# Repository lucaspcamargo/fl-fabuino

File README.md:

# FABUINO Project Files + Presentation Materials

The FABUINO is a simple arduino clone that is meant to be assembled by hand, during a workshop. It relies on an FTDI cable for programming.

This repo contains the project files and materials for presentation. The first instance of this workshop was given at FabLab Joinville in March 2020.
It was a good opportunity to project the spirit of DIY-electronics on the participants.

If anyone wants to use this for something just hit me up :)

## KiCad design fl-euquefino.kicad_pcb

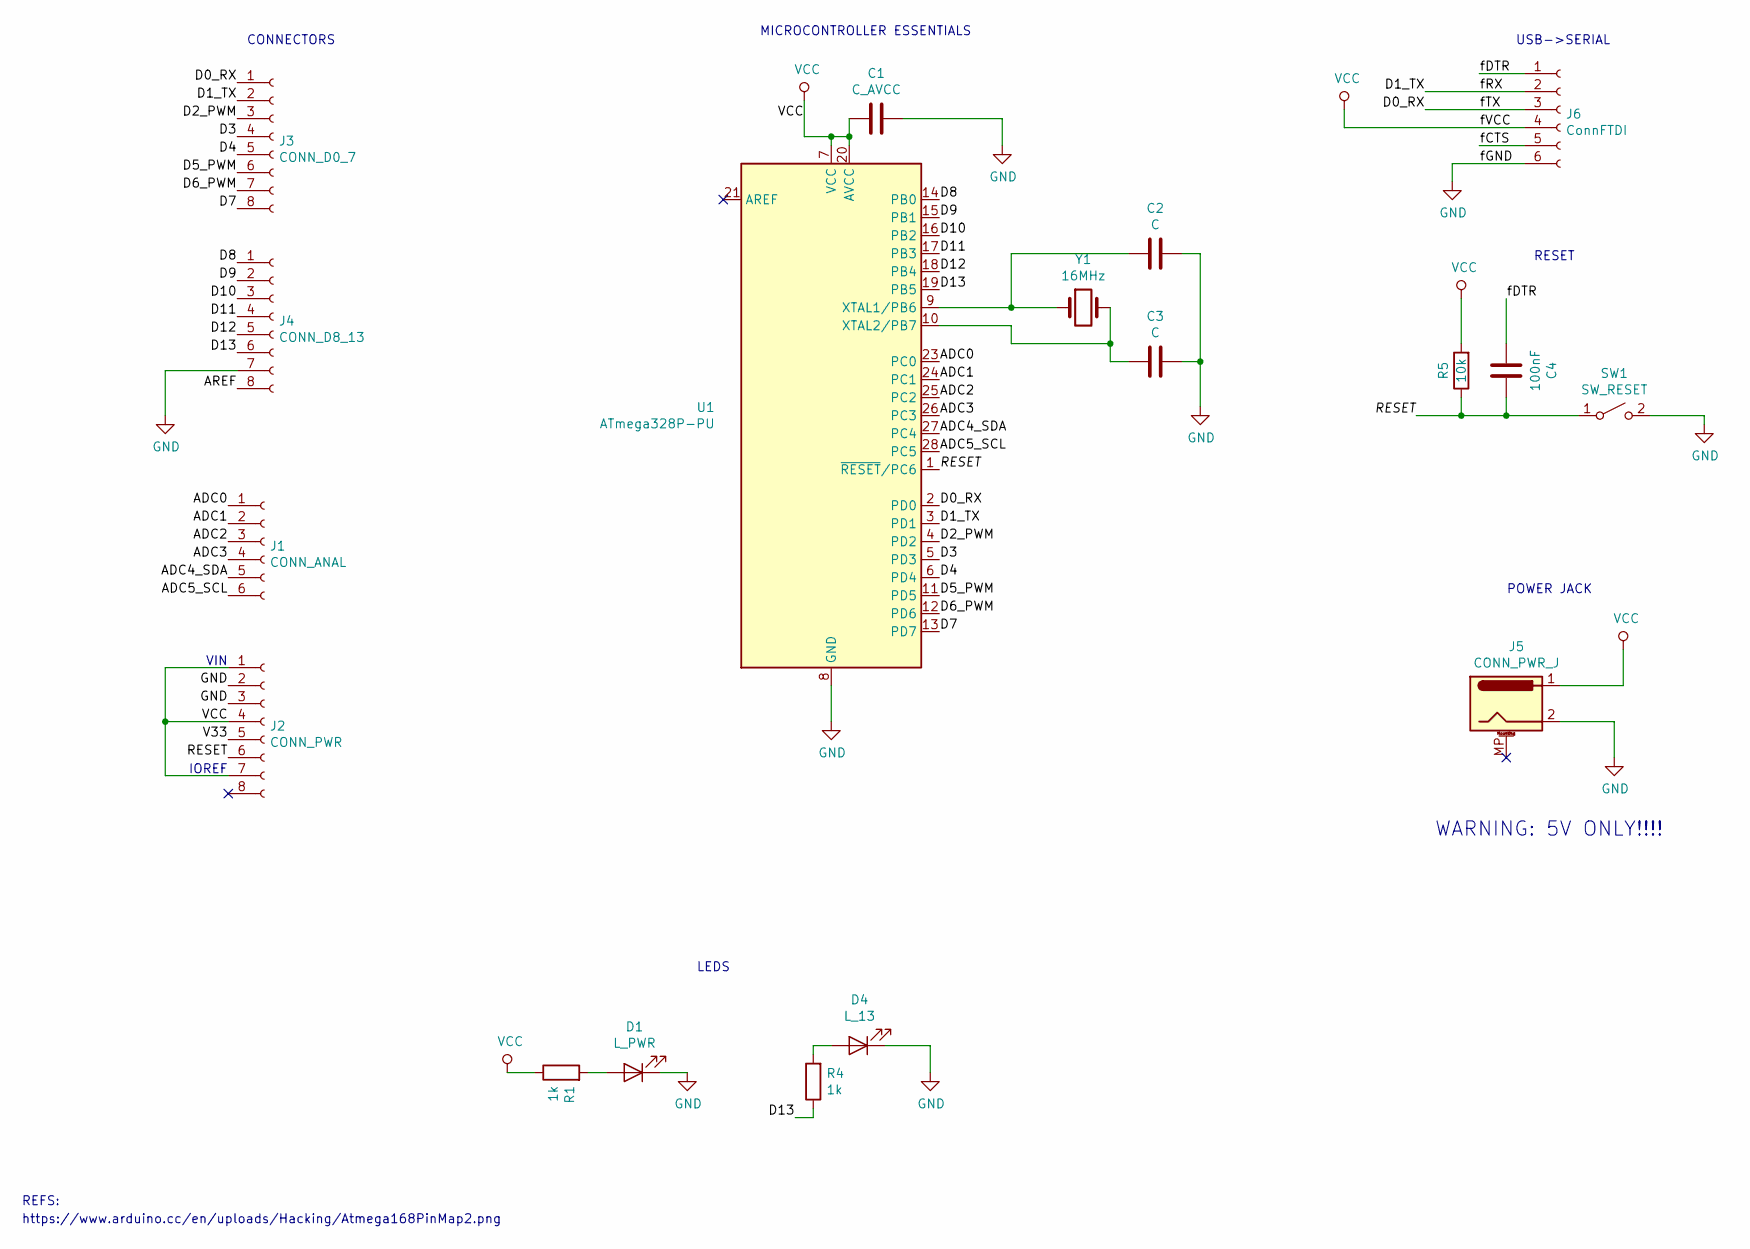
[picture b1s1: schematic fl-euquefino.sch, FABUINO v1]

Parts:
C1: C_AVCC; CP_Radial_D5.0mm_P2.50mm
C2, C3: C; C_Disc_D3.0mm_W2.0mm_P2.50mm
C4: 100nF; C_Disc_D3.0mm_W2.0mm_P2.50mm
D1: L_PWR; LED_D3.0mm
D4: L_13; LED_D3.0mm
J1: CONN_ANAL; PinHeader_1x06_P2.54mm_Vertical
J2: CONN_PWR; PinHeader_1x08_P2.54mm_Vertical
J3: CONN_D0_7; PinHeader_1x08_P2.54mm_Vertical
J4: CONN_D8_13; PinHeader_1x08_P2.54mm_Vertical
J5: CONN_PWR_J; BarrelJack_Horizontal
J6: ConnFTDI; PinHeader_1x06_P2.54mm_Vertical
R1, R4: 1k; R_Axial_DIN0207_L6.3mm_D2.5mm_P10.16mm_Horizontal
R5: 10k; R_Axial_DIN0207_L6.3mm_D2.5mm_P10.16mm_Horizontal
SW1: SW_RESET; SW_PUSH_6mm
U1: ATmega328P-PU; DIP-28_W7.62mm
Y1: 16MHz; Crystal_HC49-U_Vertical

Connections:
/ADC0: J1.1, U1.23 (PC0)
/ADC1: J1.2, U1.24 (PC1)
/ADC2: J1.3, U1.25 (PC2)
/ADC3: J1.4, U1.26 (PC3)
/ADC4_SDA: J1.5, U1.27 (PC4)
/ADC5_SCL: J1.6, U1.28 (PC5)
/AREF: J4.8
/D0_RX: J3.1, J6.3, U1.2 (PD0)
/D1_TX: J3.2, J6.2, U1.3 (PD1)
/D2_PWM: J3.3, U1.4 (PD2)
/D3: J3.4, U1.5 (PD3)
/D4: J3.5, U1.6 (PD4)
/D5_PWM: J3.6, U1.11 (PD5)
/D6_PWM: J3.7, U1.12 (PD6)
/D7: J3.8, U1.13 (PD7)
/D8: J4.1, U1.14 (PB0)
/D9: J4.2, U1.15 (PB1)
/D10: J4.3, U1.16 (PB2)
/D11: J4.4, U1.17 (PB3)
/D12: J4.5, U1.18 (PB4)
/D13: J4.6, R4.1, U1.19 (PB5)
/RESET: C4.1, J2.6, R5.1, SW1.1 (A), U1.1 (~RESET~/PC6)
/V33: J2.5
/fCTS: J6.5
/fDTR: C4.2, J6.1
GND: C1.1, C2.1, C3.1, D1.1 (K), D4.1 (K), J2.2, J2.3, J4.7, J5.2, J6.6, SW1.2 (B), U1.8 (GND), U1.22 (GND)
unnamed: C2.2, U1.9 (XTAL1/PB6), Y1.1
unnamed: C3.2, U1.10 (XTAL2/PB7), Y1.2
unnamed: D1.2 (A), R1.2
unnamed: D4.2 (A), R4.2
VCC: C1.2, J2.1, J2.4, J2.7, J5.1, J6.4, R1.1, R5.2, U1.7 (VCC), U1.20 (AVCC)

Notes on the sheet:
USB->SERIAL
MICROCONTROLLER ESSENTIALS
POWER JACK
CONNECTORS
REFS:
https://www.arduino.cc/en/uploads/Hacking/Atmega168PinMap2.png
RESET
LEDS
WARNING: 5V ONLY!!!!
IOREF
VIN

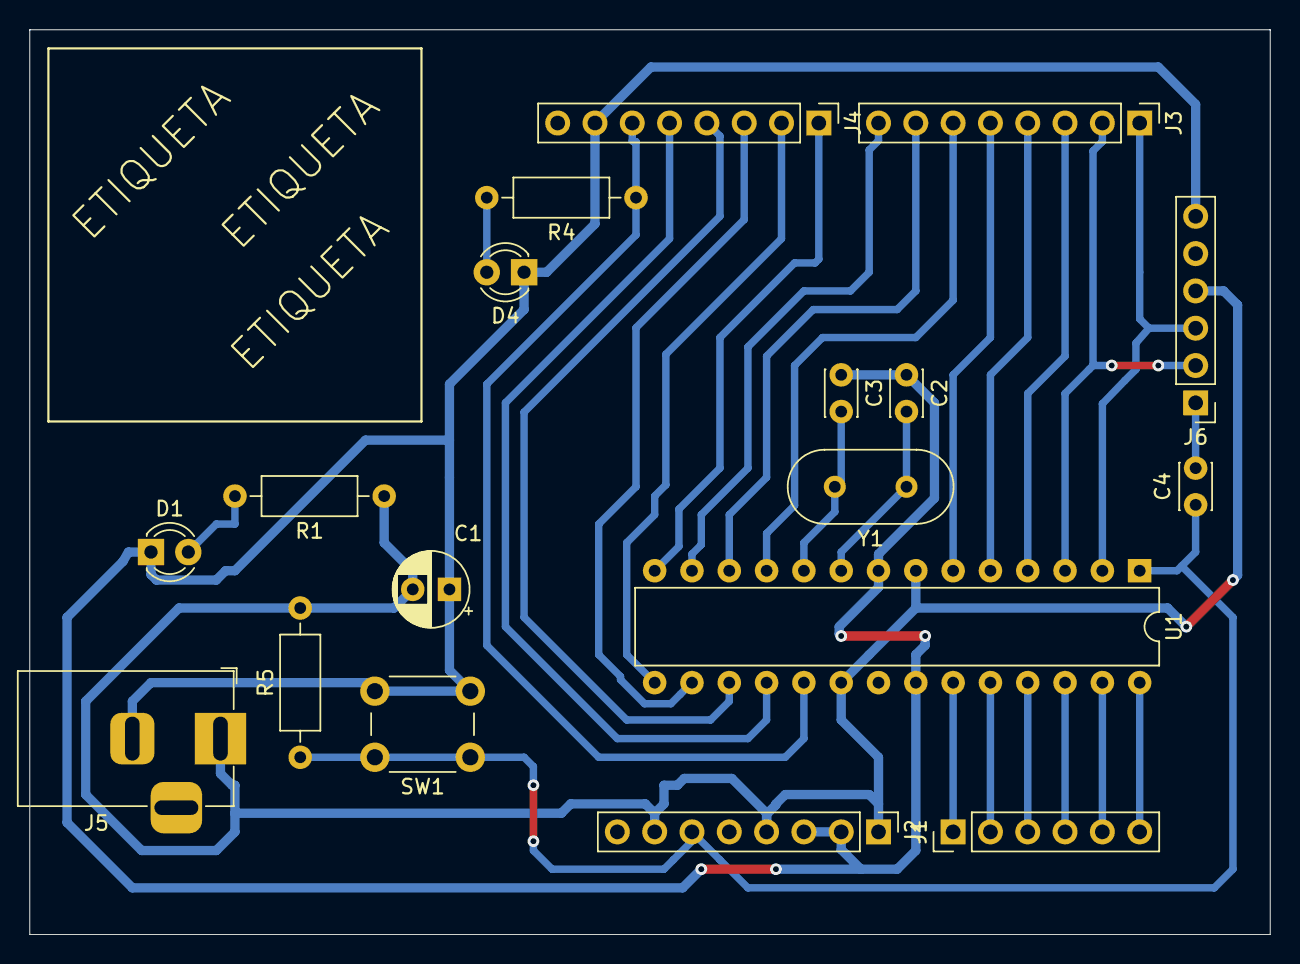
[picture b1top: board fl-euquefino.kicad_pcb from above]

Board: 2 copper layers, 84.5 x 61.6 mm, 18 parts (0 on the bottom side), 28 nets.

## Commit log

2020-03-16 initial commit to source control
2020-03-16 added readme.md
